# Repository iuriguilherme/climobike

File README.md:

ClimoBike
===

ClimoBike é uma central de monitoramento portátil da qualidade do ar e das condições climáticas, adaptável a bicicletas urbanas.  

---

Toda a documentação está na [wiki](https://op.velivery.com.br/projects/climobike/wiki).  

Projeto original: <https://github.com/smjacques/climobike>  

### Código fonte

Repositório público git:  

* <https://notabug.org/velivery/climobike>  

### Roadmap

<https://op.velivery.com.br/topics/56>

### Versões

v0.1, 2017-10-05 -- sistema de monitoramento da qualidade do ar e das condições climáticas adaptável a bicicletas, <https://github.com/smjacques/climobike>  
v0.2, 2018-06-10 -- ClimoBike + Velivery <https://notabug.org/velivery/climobike>  
v0.2.0.1, 2018-06-30 -- ESP32 Devkit + GPS, sensor de metano, sensor de gases tóxicos, sensor de umidade relativa do ar e temperatura  
v0.2.0.2, 2018-07-07 -- ESP32 Devkit v2 soldado em placa dentro de invólucro de acrílico com GPS, módulo de cartão SD, sensor de metano, sensor de gases tóxicos, sensor de dióxido de carbono, sensor de umidade relativa do ar e temperatura, buzzer, relógio, e sensor de luminosidade   

Licença
---

Copyleft 2017 Saulo Jacques  
Copyleft 2018 Velivery  

### Contribuições

- Saulo Jacques  
- Alisson Claudino  
- Desobediente Civil  

### GPL v3

**Este programa é distribuído na esperança de que possa ser útil,**
**mas SEM NENHUMA GARANTIA; sem uma garantia implícita de ADEQUAÇÃO**  
**a qualquer MERCADO ou APLICAÇÃO EM PARTICULAR. Veja a**  
**Licença Pública Geral GNU para mais detalhes.**  

**Você deve ter recebido uma cópia da Licença Pública Geral GNU junto**  
**com este programa (veja o arquivo LICENSE.md).**  
**Se não, veja <http://www.gnu.org/licenses/>.**

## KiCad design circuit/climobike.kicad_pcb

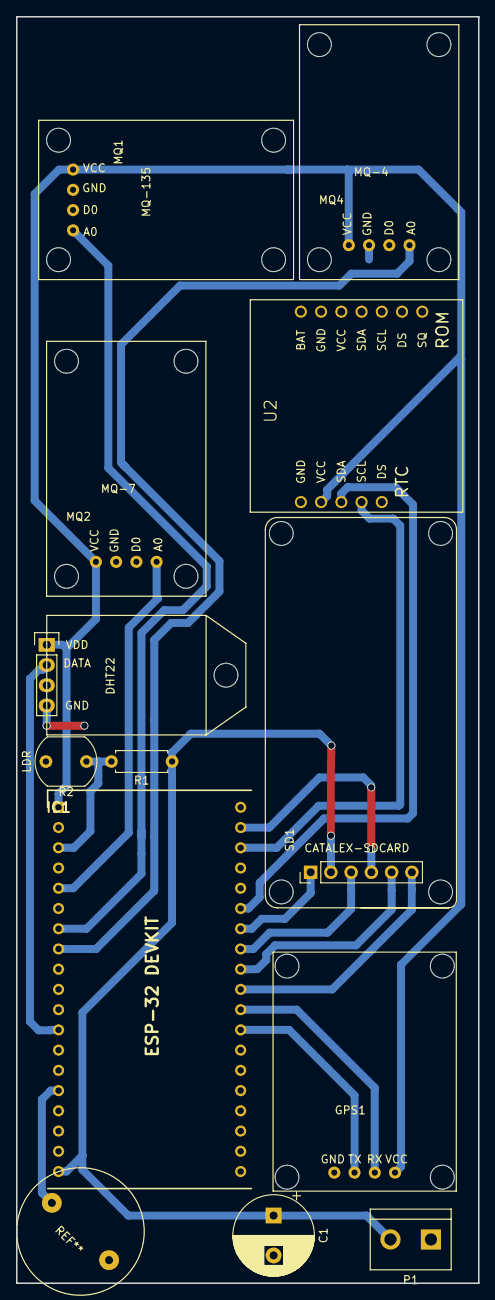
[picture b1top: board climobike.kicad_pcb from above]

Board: 2 copper layers, 58.0 x 159.0 mm, 12 parts (0 on the bottom side), 16 nets.

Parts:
C1: 1000u; CP_Radial_D10.0mm_P5.00mm
GPS1: NEO-6M; Ublox-NEO-6M
IC1: ESP32-DevKitC; ESP32-DEVKIT-C
MQ1: MQ-135; MQ-Sensor
MQ2: MQ-7; MQ-Sensor
MQ4: MQ-4; MQ-Sensor
P1: INPUT; bornier2
R1: R_SHUNT; R_Axial_DIN0207_L6.3mm_D2.5mm_P7.62mm_Horizontal
R2: LDR; R_LDR_7x6mm_P5.1mm_Vertical
SD1: U_SDCARD; CATALEX-SDCARD
U1: DHT22; DHT22_Temperature_Humidity
U2: Tiny_RTC_DS1307

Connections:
+3V3: GPS1.4, IC1.1, MQ1.4, MQ2.4, MQ4.4, U1.1, U2.9
CLOCK_SCL: IC1.36, U2.11
CLOCK_SDA: IC1.33, U2.10
CO_OUT: IC1.5, MQ2.1
DHT_PIN: IC1.12, U1.2
GND: C1.2, GPS1.1, IC1.14, IC1.32, IC1.38, MQ1.3, MQ2.3, MQ4.3, P1.1, R2.2, SD1.6, U1.4, U2.8
GPS_RX: GPS1.3, IC1.28
GPS_TX: GPS1.2, IC1.27
LDR_V: IC1.3, R1.2, R2.1
MET_OUT: IC1.8, MQ4.1
SD_CLK: IC1.30, SD1.2
SD_CS: IC1.29, SD1.1
SD_MISO: IC1.31, SD1.4
SD_MOSI: IC1.37, SD1.3
TOX_OUT: IC1.7, MQ1.1
VCC: C1.1, IC1.19, P1.2, R1.1, SD1.5

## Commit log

2018-06-10 ADD: GPS RAW code
2018-06-10 Sois vós
2018-06-15 ADD: SDCARD code
2018-06-15 ADD: components symbols and connections
2018-06-19 ADD: ESP32 raw code + Wifi Connect
2018-06-21 ADD: WiFi data send code
2018-06-27 ADD: Sdcard + Clock + Sensors + Wifi complete configure
2018-06-27 ADD: pin map
2018-06-27 ADD: required libs and custom SD lib
2018-06-28 Arquivos do python, platformio, etc.
2018-06-28 Redundância
2018-06-28 Porra de platformio init
2018-06-28 submodule TinyGPSPlus
2018-06-28 Cosmética
2018-06-28 GPS includes
2018-06-28 Testando lib TinyGPS
2018-06-28 Mais testes com platformio
2018-06-28 Mais arrumacao de codigo
2018-06-29 Teroicamente deu certo agora
2018-06-30 ADD: Other Sensors MAP+Code
2018-06-30 ADD: Circuit Schematic + KiCad Libs
2018-06-30 Removidas mensagens de DEBUG
2018-06-30 Atualizando LEIAME
2018-07-02 Enviando testes para repositório
2018-07-03 Versão GPS funcionando de fato
2018-07-03 ADD: Full circuit schematic and pcb design
2018-07-03 Modularizando eu posso desmodularizar
2018-07-03 Fiz um gráfico de LDR em python
2018-07-03 Desmodularizando eu posso modularizar
2018-07-03 Consertando erros de compilação
2018-07-03 Ligando sensores de gás e dht
2018-07-03 ADD: set clock code
2018-07-03 EDIT: files
2018-07-03 Arrumando wifi e relógio
2018-07-03 Ativando Cartão SD
2018-07-04 Formatação
2018-07-04 Ligando relógio
2018-07-04 ver se a ordem dos tratores altera o atropelamento
2018-07-04 ADD: Super Mario Easter EGG Sound
2018-07-04 Atualizando hora
2018-07-04 ::trollface::
2018-07-04 -"Putz cara, como é que tu faz uma coisa dessa"
2018-07-04 Pressa de trollar da nisso
2018-07-04 Ainda não ta 100%
2018-07-04 Testando Wire transmission
2018-07-04 Esperançosamente consertando o relógio
2018-07-04 Modulando saída serial
2018-07-04 Preciosismo
2018-07-04 Elaborando primeiro teste
2018-07-04 Preparando segundo teste
2018-07-04 Tentando escrever linha a linha
2018-07-04 Nada como ler o manual
2018-07-04 Abortando o teste de gravação e retornando ao teste1
2018-07-04 Agora sim teste1
2018-07-04 Consertando lógica dos testes
2018-07-04 Commit sem compilar é sono
2018-07-04 ADD: Fabrication files
2018-07-04 Modelo de dados v0.2
2018-07-04 retomando os testes
2018-07-04 Testando somente o pertinente
2018-07-04 Copiando o código inteiro para o teste
2018-07-04 Aprofundando testes com energia
2018-07-04 Atualizando rotinas padrão do Relógio
2018-07-04 Adaptando testes
2018-07-04 Reorganizando arquivos
2018-07-04 Corrigindo erros de compilação
2018-07-04 Alterando versão e revisão
2018-07-04 Sucesso no teste2
2018-07-04 Preparando para o sucesso
2018-07-04 Teste 2 em produção
2018-07-04 Próximo passo para o teste 2
2018-07-04 Consertando variáveis
2018-07-04 Testando Strings
2018-07-04 Teste2 realizado
2018-07-06 De novo: trollada com pressa da nisso
2018-07-06 Separando HTTP e Wifi
2018-07-06 Enviando para produção
2018-07-08 Introduzindo dados falsos para teste
2018-07-09 Arquivos fora do último push
2018-07-09 Lançando v0.2.0.2
2018-07-11 ADD: Classes, EDIT: SD functionality, DEL: Garbage .hpp files
2018-07-17 ADD: full data parsing to sdcard (to each 10 minutes)
